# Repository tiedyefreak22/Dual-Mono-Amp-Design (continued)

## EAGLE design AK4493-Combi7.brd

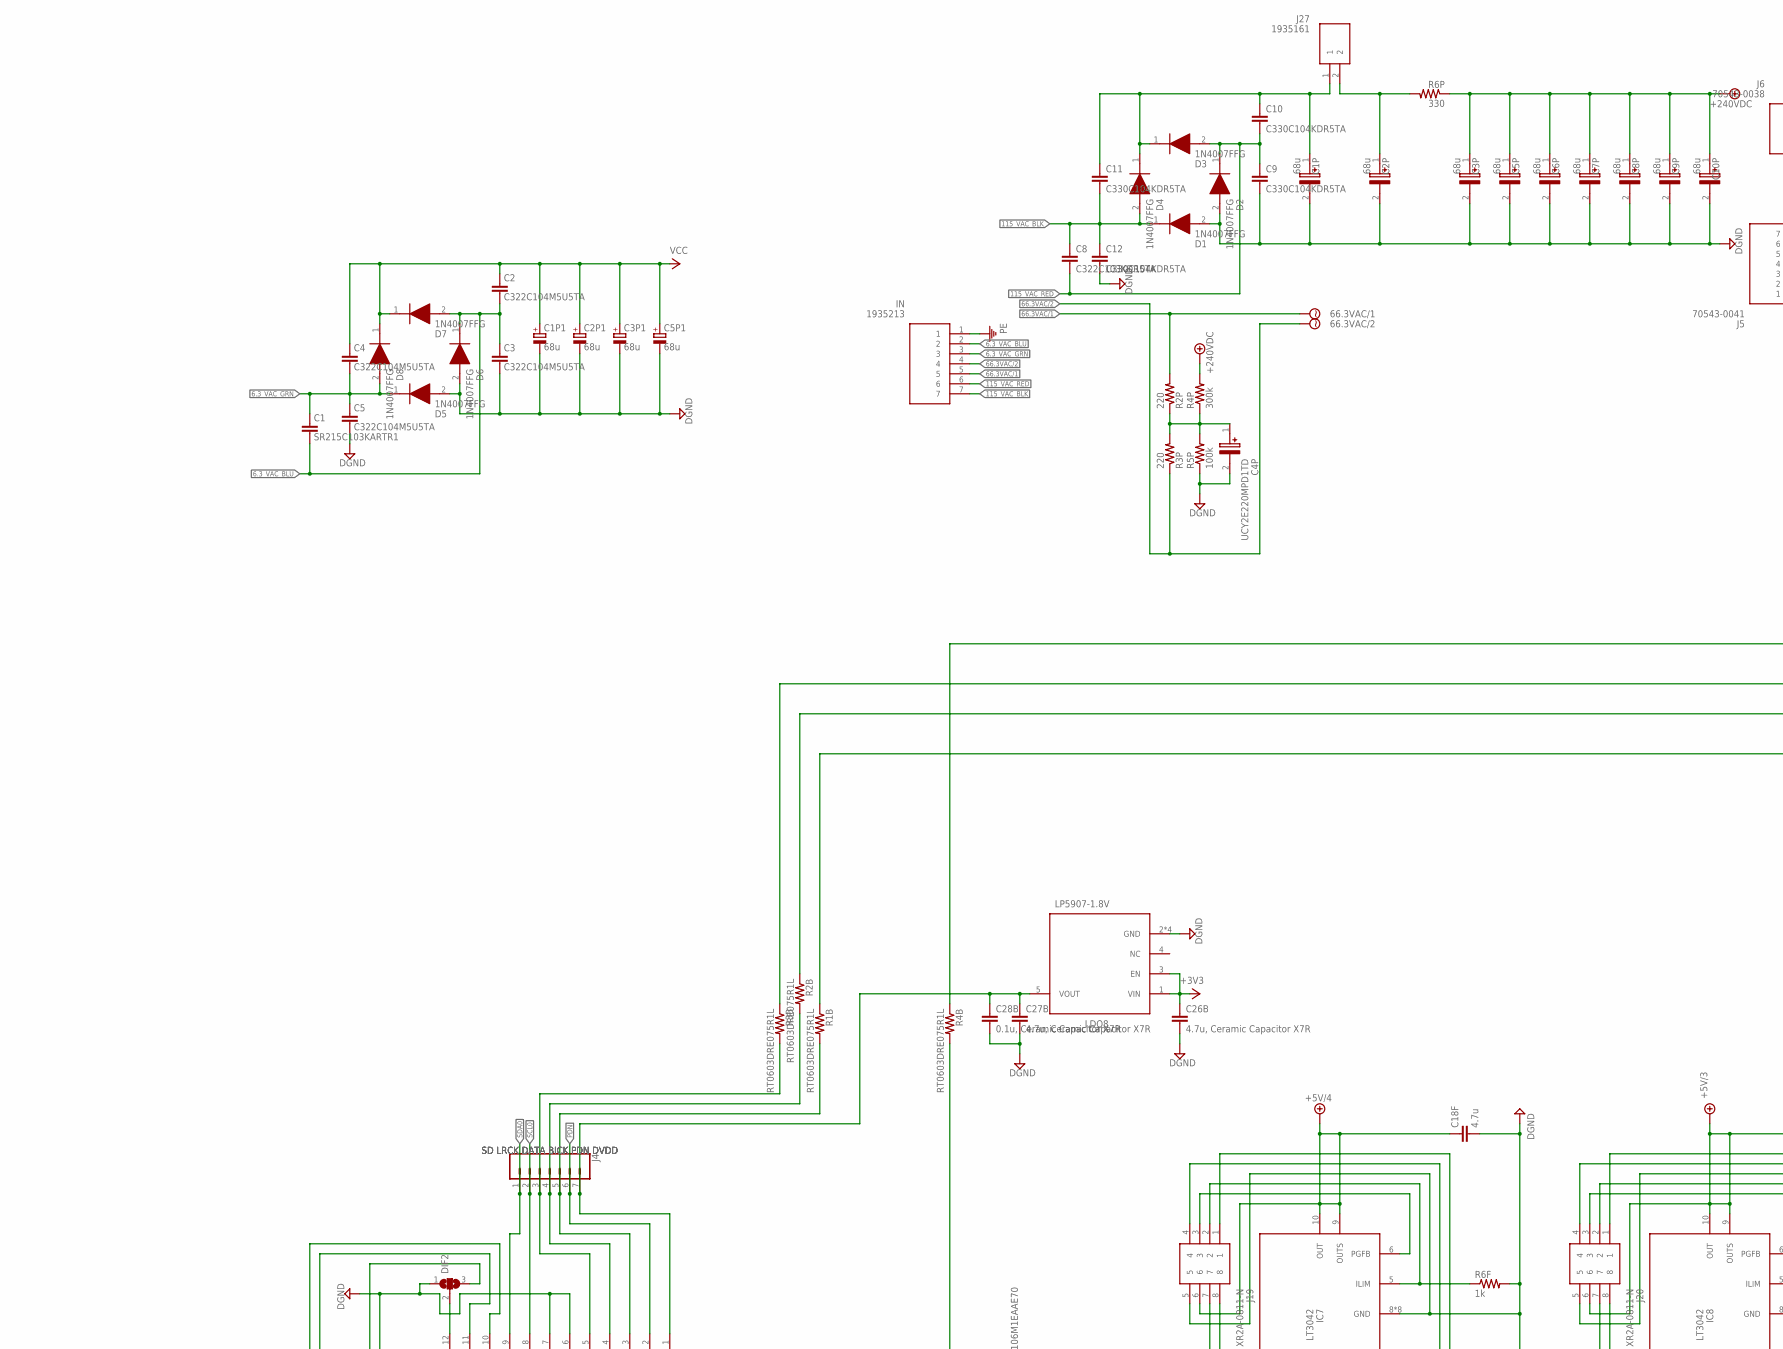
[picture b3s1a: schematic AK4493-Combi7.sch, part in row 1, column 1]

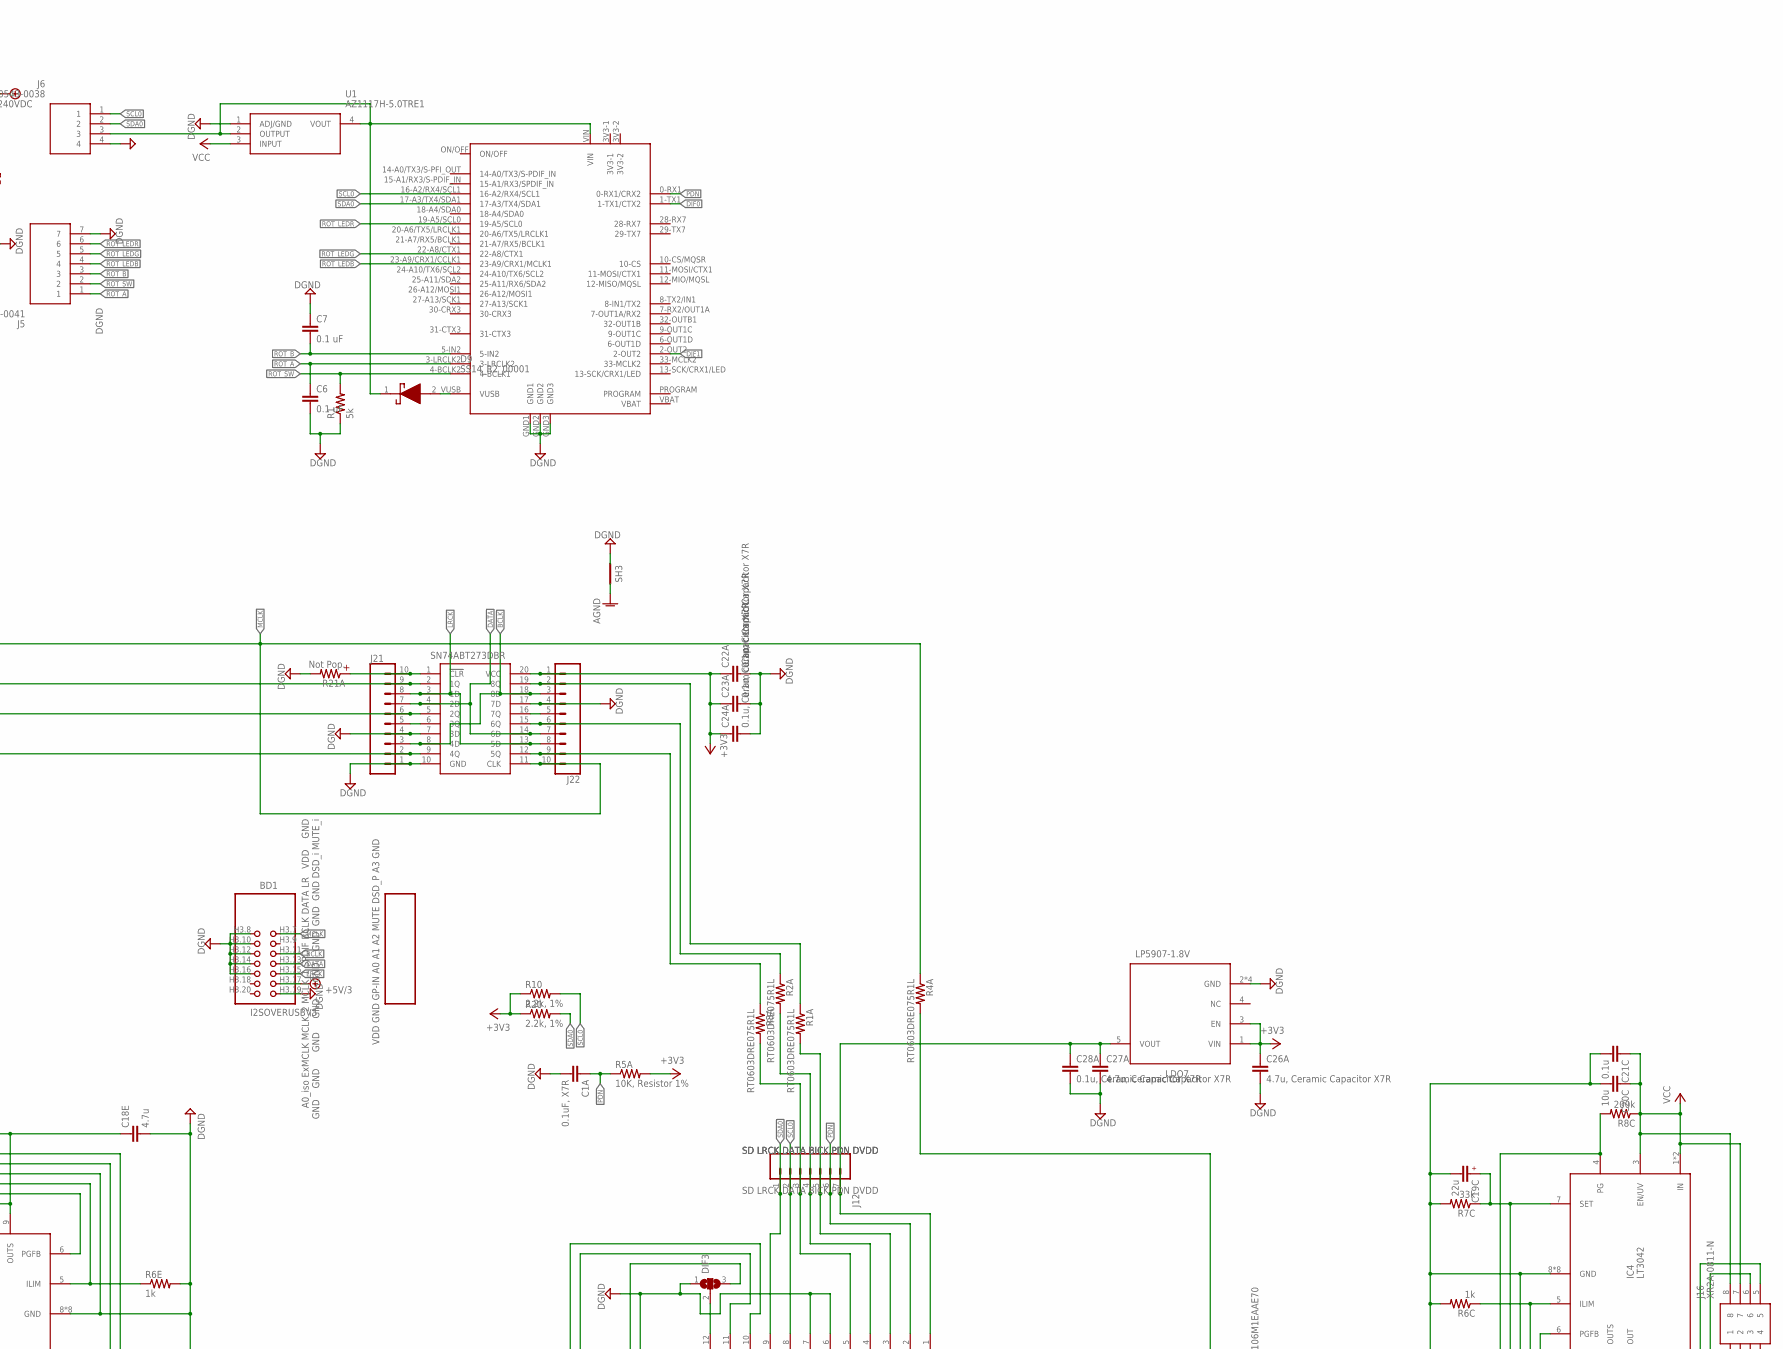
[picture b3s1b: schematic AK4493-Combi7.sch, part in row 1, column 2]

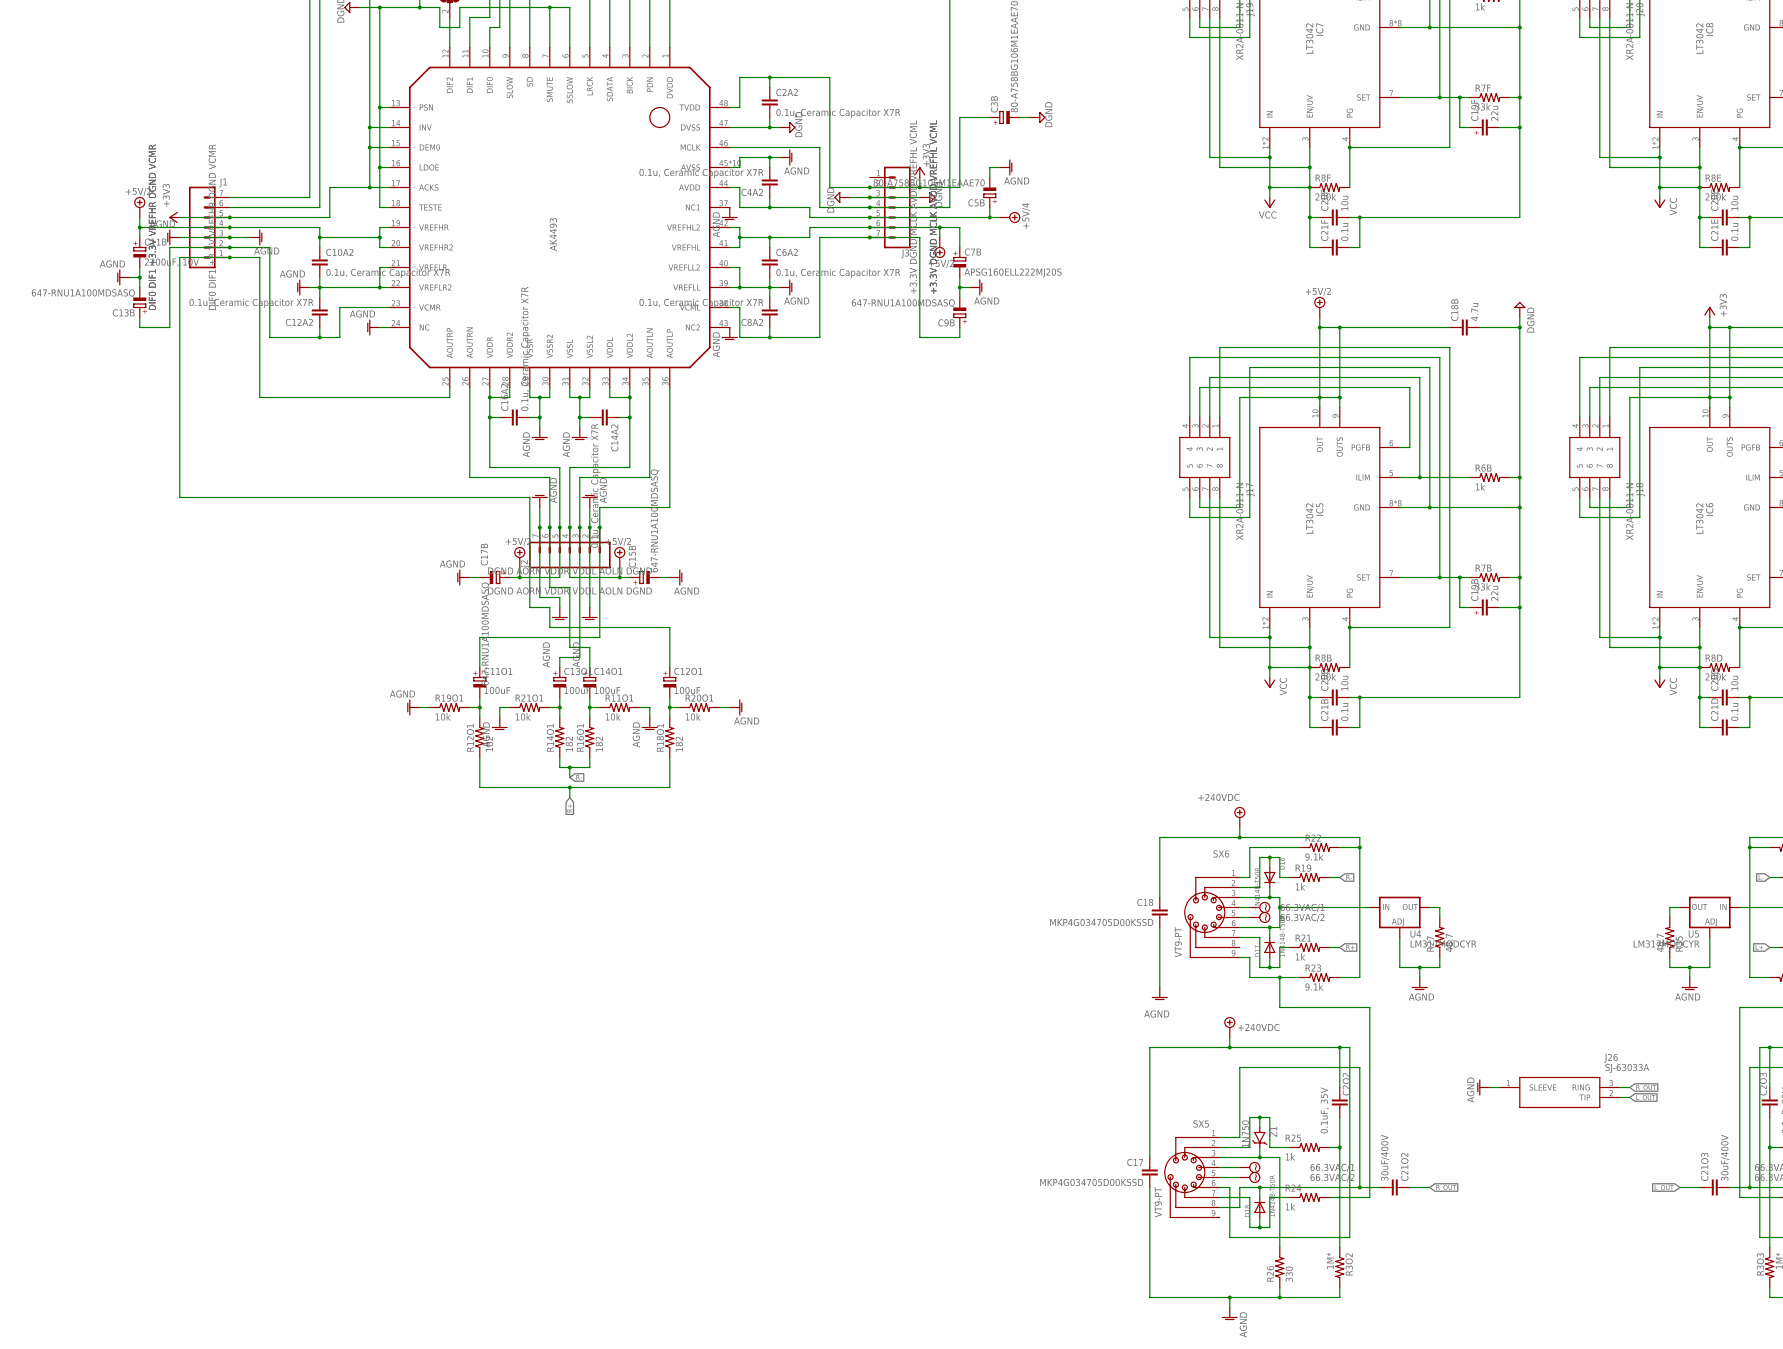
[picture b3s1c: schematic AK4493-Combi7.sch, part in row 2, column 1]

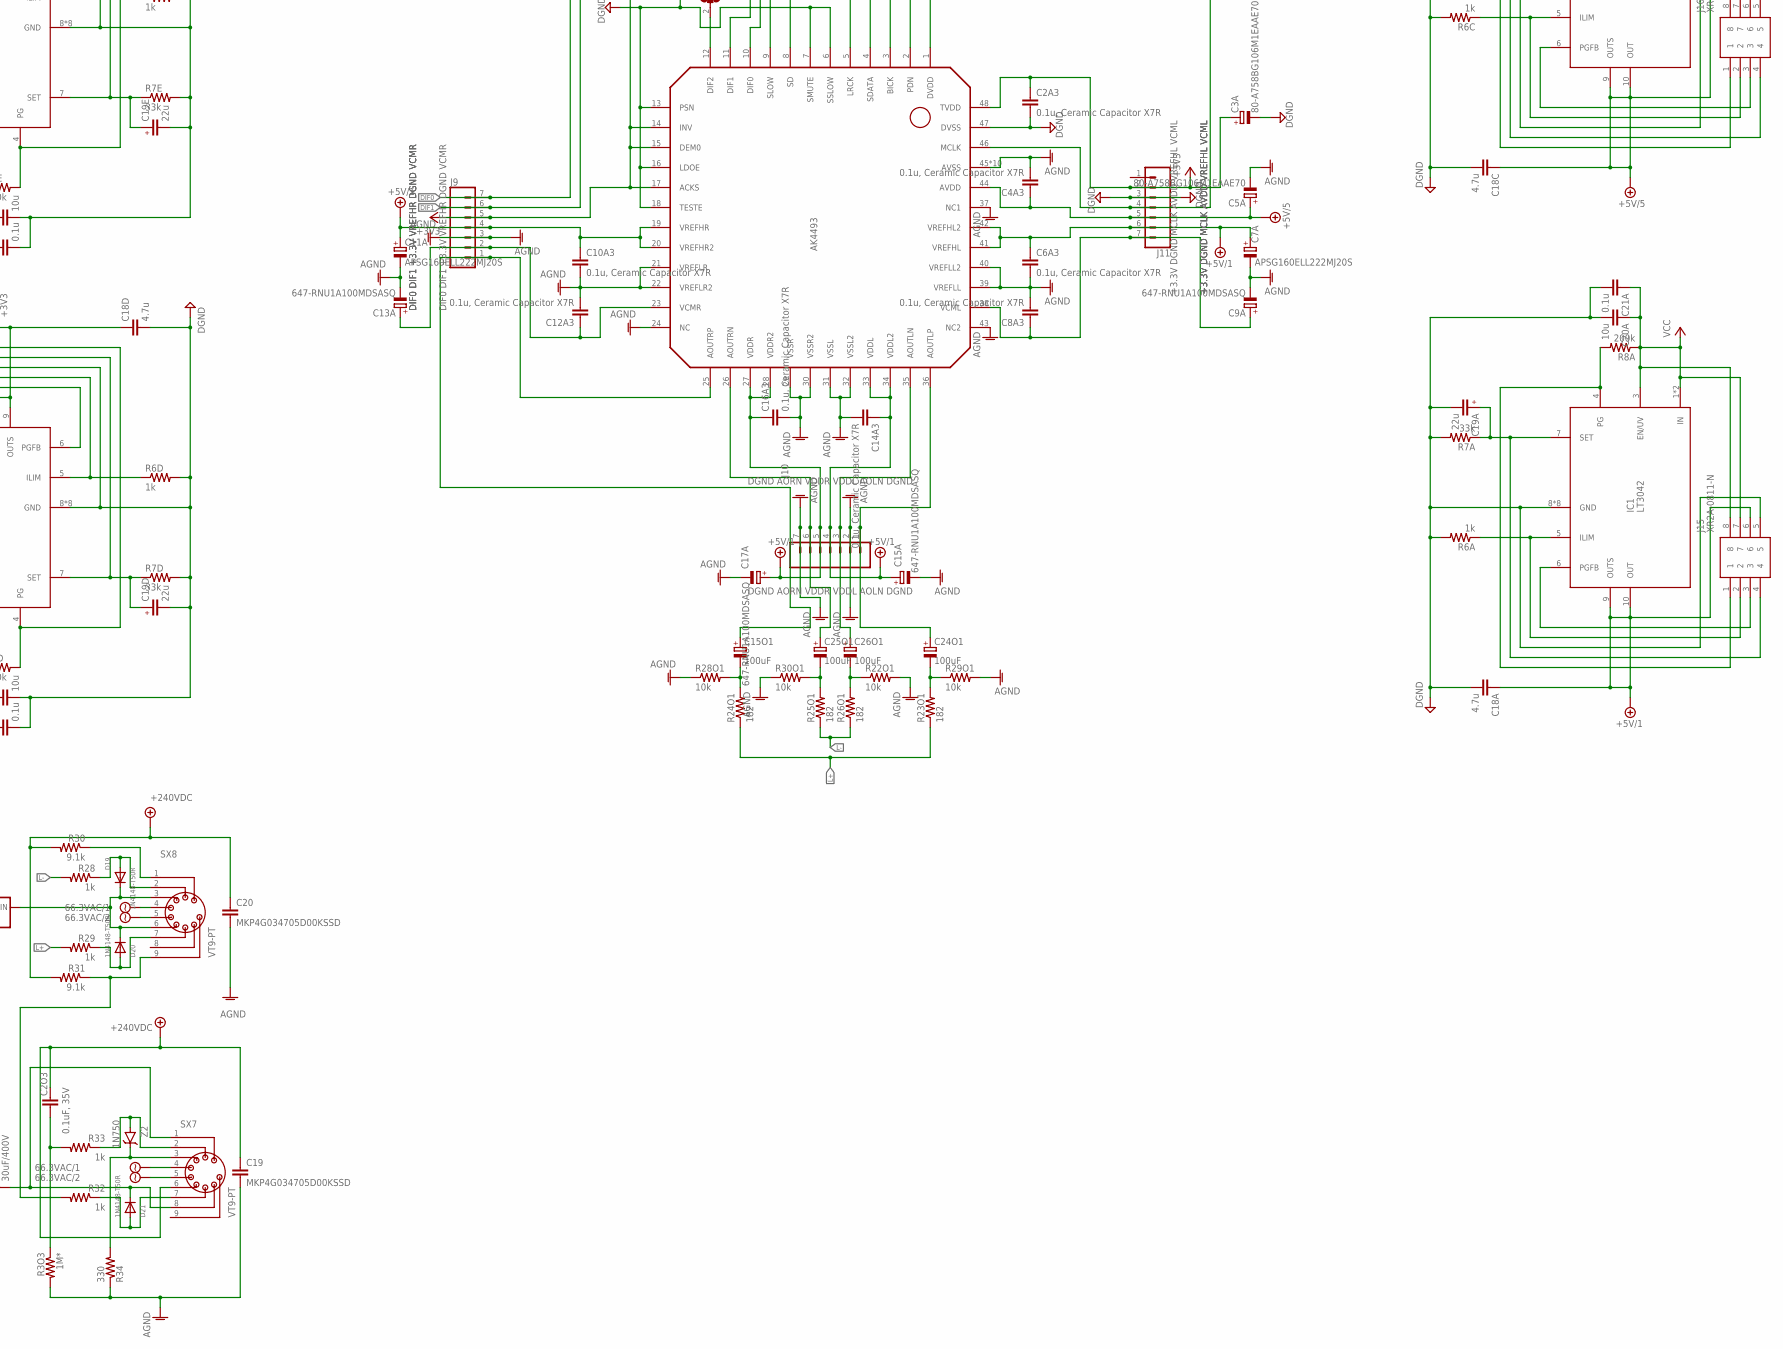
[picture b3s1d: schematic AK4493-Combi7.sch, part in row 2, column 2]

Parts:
BD1: I2SOVERUSBV3
C1: SR215C103KARTR1; SR211C104KARTR1
C1A: 0.1uF, X7R; CAPC2012X135N
C1P, C2P, C3P, C5P, C6P, C7P, C8P, C9P, C10P: 68u; CAPPRD750W80D1475H4700
C1P1, C2P1, C3P1, C5P1: 68u; CAPPRD750W80D1825H3750
C2, C3, C4, C5: C322C104M5U5TA; C322C104K1R5TA
C2A2, C2A3, C4A2, C4A3, C6A2, C6A3, C8A2, C8A3, C10A2, C10A3, C12A2, C12A3, C14A2, C14A3, C16A2, C16A3: 0.1u, Ceramic Capacitor X7R; CAPC1608X95N
C2O2, C2O3: 0.1uF, 35V; MKS4B031002A00JC00
C3A: 80-A758BG106M1EAAE70; CAPPRD150W45D450H600
C3B, C5A, C5B: 80-A758BG106M1EAAE70; CAPPRD200W55D500H800
C4P: UCY2E220MPD1TD; CAPPRD500W60D1025H1750
C6, C7: 0.1 uF; CAPC2012X135N
C7A, C7B, C11A: APSG160ELL222MJ20S; CAPPRD500W60D1025H2150
C8: C322C103KDR5TA; C322C101JCG5TA7301
C9, C10, C11, C12: C330C104KDR5TA
C9A, C9B, C13A, C13B, C15A, C15B, C17A, C17B: 647-RNU1A100MDSASQ; CAPPRD150W45D450H600
C11B: 2200uF, 10V; CAPPRD500W60D1025H2150
C11O1, C12O1, C13O1, C14O1, C15O1, C24O1, C25O1, C26O1: 100uF; CAPPRD350W60D825H1300
C17, C18, C19, C20: MKP4G034705D00KSSD
C18A, C18B, C18C, C18D, C18E, C18F: 4.7u; CAPC2013X140N
C19A, C19B, C19C, C19D, C19E, C19F: 22u; C1206
C20A, C20B, C20C, C20D, C20E, C20F: 10u; CAPC2012X135N
C21A, C21B, C21C, C21D, C21E, C21F: 0.1u; CAPC2012X135N
C21O2, C21O3: 30uF/400V; DCP4G053006ID2KSSD
C22A, C23A, C24A, C28A, C28B: 0.1u, Ceramic Capacitor X7R; CAPC2012X135N
C26A, C26B, C27A, C27B: 4.7u, Ceramic Capacitor X7R; CAPC2013X140N
D1, D2, D3, D4, D5, D6, D7, D8: 1N4007FFG; DIOAD1405W86L465D235
D9: SS14_R2_00001; DIOM5027X244N
D16, D17, D18, D19, D20, D21: 1N4148-T50R; DIOAD1068W53L380D172
DIF2, DIF3: SJ2W; SJ_2
IC1, IC4, IC5, IC6, IC7, IC8: LT3042; SOP50P490X110-11N
IC3, IC9: AK4493; LQFP48_
IC4A: SN74ABT273DBR; SOP65P780X200-20N
IN: 1935213
J1, J2, J3, J4, J9, J10, J11, J12: CONN_07; 1X07
J5: 70543-0041; SHDR7W64P0X254_1X7_2033X508X11
J6: 70543-0038; SHDR4W64P0X254_1X4_1271X660X11
J15, J16, J17, J18, J19, J20: XR2A-0811-N; DIPS762W51P254L1016H390Q8N
J21, J22: CONN_10"; 1X10
J26: SJ-63033A; SJ63033A
J27: 1935161
LDO7, LDO8: LP5907-1.8V; SOT95P280X145-5N
R1: 5k; ERJP06D1000V
R1A, R1B, R2A, R2B, R3A, R3B, R4A, R4B: RT0603DRE075R1L; RESC1608X55N
R2P, R3P: 220; 0411/15
R3O2, R3O3: 1M*; 0207/10
R4P: 300k; 0411/15
R5A: 10K, Resistor 1%; RESC2012X50N
R5P: 100k; 0411/15
R6A, R6B, R6C, R6D, R6E, R6F: 1k; RESC2012X60N
R6P: 330; 0411/15
R7A, R7B, R7C, R7D, R7E, R7F: 33k; R0805
R8A, R8B, R8C, R8D, R8E, R8F: 200k; R0805
R10, R20: 2.2k, 1%; RCS0805_E3
R11O1, R19O1, R20O1, R21O1, R22O1, R28O1, R29O1, R30O1: 10k; 0207/10
R12O1, R14O1, R16O1, R18O1, R23O1, R24O1, R25O1, R26O1: 182; 0207/10
R19, R21, R24, R25, R28, R29, R32, R33: 1k; 0207/10
R21A: Not Pop.; R0805-POL
R22, R23, R30, R31: 9.1k; 0411/15
R26, R34: 330; 0207/10
R27, R35: 48.7; 0207/10
SH3: SHORTA5; SHORT_ALL-50
SX5, SX6, SX7, SX8: VT9-PT
U1: AZ1117H-5.0TRE1; SOT230P700X180-4N@1
U4, U5: LM317MQDCYR; SOT230P700X180-4N
U$1: TEENSY40
Z1, Z2: 1N750; DIOAD1256W56L444D203

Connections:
6.3_VAC_BLU: C1.2, C2.2, C3.1, D6.1 (K), D7.2 (A), IN.2
6.3_VAC_GRN: C1.1, C4.2, C5.1, D5.1 (K), D8.2 (A), IN.3
66.3VAC/1: IN.5, R2P.2, SX5.4, SX6.4, SX7.4, SX8.4
66.3VAC/2: IN.4, R3P.1, SX5.5, SX6.5, SX7.5, SX8.5
115_VAC_BLK: C8.1, C11.2, C12.1, D1.1 (K), D4.2 (A), IN.7
115_VAC_RED: C8.2, C9.1, C10.2, D2.1 (K), D3.2 (A), IN.6
+3V3: C2A2.1, C2A3.1, C3A.1 (+), C3B.1 (+), C18D.1, C22A.1, C23A.1, C24A.1, C26A.1, C26B.1, DIF2.3, DIF3.3, IC3.14 (INV), IC3.15 (DEM0), IC3.17 (ACKS), IC3.48 (TVDD), IC4A.20 (VCC), IC6.9 (OUTS), IC6.10 (OUT), IC9.14 (INV), IC9.15 (DEM0), IC9.17 (ACKS), IC9.48 (TVDD), J1.5, J3.2, J9.5, J11.2, J18.6, J22.1, LDO7.1 (VIN), LDO7.3 (EN), LDO8.1 (VIN), LDO8.3 (EN), R5A.2, R10.1, R20.1
+5V/1: C6A3.1, C7A.1 (+), C10A3.1, C11A.1 (+), C14A3.1, C15A.1 (+), C16A3.1, C17A.1 (+), C18A.1, IC1.9 (OUTS), IC1.10 (OUT), IC9.19 (VREFHR), IC9.20 (VREFHR2), IC9.27 (VDDR), IC9.28 (VDDR2), IC9.33 (VDDL), IC9.34 (VDDL2), IC9.41 (VREFHL), IC9.42 (VREFHL2), J9.4, J10.4, J10.5, J11.6, J15.6
+5V/2: C6A2.1, C7B.1 (+), C10A2.1, C11B.1 (+), C14A2.1, C15B.1 (+), C16A2.1, C17B.1 (+), C18B.1, IC3.19 (VREFHR), IC3.20 (VREFHR2), IC3.27 (VDDR), IC3.28 (VDDR2), IC3.33 (VDDL), IC3.34 (VDDL2), IC3.41 (VREFHL), IC3.42 (VREFHL2), IC5.9 (OUTS), IC5.10 (OUT), J1.4, J2.4, J2.5, J3.6, J17.6
+5V/3: BD1.H3.17, C18E.1, IC8.9 (OUTS), IC8.10 (OUT), J20.6
+5V/4: C4A2.1, C5B.1 (+), C18F.1, IC3.44 (AVDD), IC7.9 (OUTS), IC7.10 (OUT), J3.5, J19.6
+5V/5: C4A3.1, C5A.1 (+), C18C.1, IC4.9 (OUTS), IC4.10 (OUT), IC9.44 (AVDD), J11.5, J16.6
+240VDC: C2O2.1, C2O3.1, C3P.1 (+), C5P.1 (+), C6P.1 (+), C7P.1 (+), C8P.1 (+), C9P.1 (+), C10P.1 (+), C17.1, C18.1, C19.1, C20.1, R4P.2, R6P.1, R22.2, R23.2, R30.2, R31.2, SX5.6, SX7.6
AGND: C4A2.2, C4A3.2, C5A.2 (-), C5B.2 (-), C6A2.2, C6A3.2, C7A.2 (-), C7B.2 (-), C8A2.2, C8A3.2, C9A.2 (-), C9B.2 (-), C10A2.2, C10A3.2, C11A.2 (-), C11B.2 (-), C12A2.2, C12A3.2, C13A.2 (-), C13B.2 (-), C14A2.2, C14A3.2, C15A.2 (-), C15B.2 (-), C16A2.2, C16A3.2, C17.2, C17A.2 (-), C17B.2 (-), C18.2, C19.2, C20.2, IC3.21 (VREFLR), IC3.22 (VREFLR2), IC3.24 (NC), IC3.29 (VSSR), IC3.30 (VSSR2), IC3.31 (VSSL), IC3.32 (VSSL2), IC3.37 (NC1), IC3.39 (VREFLL), IC3.40 (VREFLL2), IC3.43 (NC2), IC3.45 (AVSS), IC3.P$1 (AVSS), IC3.P$2 (AVSS), IC3.P$4 (AVSS), IC3.P$6 (AVSS), IC3.P$8 (AVSS), IC3.P$10 (AVSS), IC3.P$17 (AVSS), IC3.P$18 (AVSS), IC3.P$25 (AVSS), IC9.21 (VREFLR), IC9.22 (VREFLR2), IC9.24 (NC), IC9.29 (VSSR), IC9.30 (VSSR2), IC9.31 (VSSL), IC9.32 (VSSL2), IC9.37 (NC1), IC9.39 (VREFLL), IC9.40 (VREFLL2), IC9.43 (NC2), IC9.45 (AVSS), IC9.P$1 (AVSS), IC9.P$2 (AVSS), IC9.P$4 (AVSS), IC9.P$6 (AVSS), IC9.P$8 (AVSS), IC9.P$10 (AVSS), IC9.P$17 (AVSS), IC9.P$18 (AVSS), IC9.P$25 (AVSS), J1.3, J2.2, J2.7, J9.3, J10.2, J10.7, J26.1 (SLEEVE), R3O2.2, R3O3.2, R11O1.2, R19O1.1, R20O1.2, R21O1.1, R22O1.2, R26.1, R27.1, R28O1.1, R29O1.2, R30O1.1, R34.1, R35.1, SH3.2, U4.1 (ADJ), U5.1 (ADJ)
BCLK: BD1.H3.11, IC4A.8 (4D), IC4A.18 (8D), J21.3, J22.3
DATA: BD1.H3.13, IC4A.4 (2D), IC4A.14 (6D), J21.7, J22.7
DGND: BD1.H3.8, BD1.H3.10, BD1.H3.12, BD1.H3.14, BD1.H3.16, BD1.H3.19, C1A.2, C1P.2 (-), C1P1.2 (-), C2A2.2, C2A3.2, C2P.2 (-), C2P1.2 (-), C3.2, C3A.2 (-), C3B.2 (-), C3P.2 (-), C3P1.2 (-), C4P.2 (-), C5.2, C5P.2 (-), C5P1.2 (-), C6.2, C6P.2 (-), C7.1, C7P.2 (-), C8P.2 (-), C9.2, C9P.2 (-), C10P.2 (-), C12.2, C18A.2, C18B.2, C18C.2, C18D.2, C18E.2, C18F.2, C19A.2, C19A.3 (2), C19B.2, C19B.3 (2), C19C.2, C19C.3 (2), C19D.2, C19D.3 (2), C19E.2, C19E.3 (2), C19F.2, C19F.3 (2), C20A.2, C20B.2, C20C.2, C20D.2, C20E.2, C20F.2, C21A.2, C21B.2, C21C.2, C21D.2, C21E.2, C21F.2, C22A.2, C23A.2, C24A.2, C26A.2, C26B.2, C27A.2, C27B.2, C28A.2, C28B.2, D1.2 (A), D2.2 (A), D5.2 (A), D6.2 (A), DIF2.1, DIF3.1, IC1.8 (GND), IC1.11 (GND), IC1.P$1 (GND), IC1.P$2 (GND), IC1.P$3 (GND), IC1.P$4 (GND), IC1.P$5 (GND), IC1.P$6 (GND), IC3.6 (SSLOW), IC3.7 (SMUTE), IC3.13 (PSN), IC3.16 (LDOE), IC3.18 (TESTE), IC3.47 (DVSS), IC4.8 (GND), IC4.11 (GND), IC4.P$1 (GND), IC4.P$2 (GND), IC4.P$3 (GND), IC4.P$4 (GND), IC4.P$5 (GND), IC4.P$6 (GND), IC4A.7 (3D), IC4A.10 (GND), IC4A.17 (7D), IC5.8 (GND), IC5.11 (GND), IC5.P$1 (GND), IC5.P$2 (GND), IC5.P$3 (GND), IC5.P$4 (GND), IC5.P$5 (GND), IC5.P$6 (GND), IC6.8 (GND), IC6.11 (GND), IC6.P$1 (GND), IC6.P$2 (GND), IC6.P$3 (GND), IC6.P$4 (GND), IC6.P$5 (GND), IC6.P$6 (GND), IC7.8 (GND), IC7.11 (GND), IC7.P$1 (GND), IC7.P$2 (GND), IC7.P$3 (GND), IC7.P$4 (GND), IC7.P$5 (GND), IC7.P$6 (GND), IC8.8 (GND), IC8.11 (GND), IC8.P$1 (GND), IC8.P$2 (GND), IC8.P$3 (GND), IC8.P$4 (GND), IC8.P$5 (GND), IC8.P$6 (GND), IC9.6 (SSLOW), IC9.7 (SMUTE), IC9.13 (PSN), IC9.16 (LDOE), IC9.18 (TESTE), IC9.47 (DVSS), J3.3, J5.7, J6.4, J11.3, J15.5, J16.5, J17.5, J18.5, J19.5, J20.5, J21.1, J21.4, J22.4, LDO7.2 (GND), LDO7.6 (GND), LDO7.7 (GND), LDO7.8 (GND), LDO8.2 (GND), LDO8.6 (GND), LDO8.7 (GND), LDO8.8 (GND), R1.1, R5P.1, R6A.2, R6B.2, R6C.2, R6D.2, R6E.2, R6F.2, R7A.2, R7B.2, R7C.2, R7D.2, R7E.2, R7F.2, R21A.2, R21A.3 (2), SH3.1, U1.1 (ADJ/GND), U$1.GND1, U$1.GND2, U$1.GND3
DIF0: IC9.10 (DIF0), J9.7, U$1.1-TX1 (1-TX1/CTX2)
DIF1: IC9.11 (DIF1), J9.6, U$1.2-OUT2
L+: R23O1.1, R24O1.1, R29.2
L-: R25O1.1, R26O1.1, R28.2
LRCK: BD1.H3.15, IC4A.3 (1D), IC4A.13 (5D), J21.8, J22.8
L_OUT: C21O3.1, J26.2 (TIP)
MCLK: BD1.H3.7, IC4A.11 (CLK), J22.10, R4A.1, R4B.1
unnamed: IC4A.1 (!CLR), J21.10, R21A.1
unnamed: C8A2.1, C9B.1 (+), IC3.38 (VCML), J3.7
unnamed: IC4A.6 (3Q), J21.5
unnamed: IC4A.16 (7Q), J22.5
unnamed: C19A.1, IC1.7 (SET), J15.4, R7A.1
unnamed: D9.2 (A), U$1.VUSB
unnamed: IC5.4 (PG), J17.1, R8B.2
unnamed: IC5.6 (PGFB), J17.3
unnamed: C12A3.1, C13A.1 (+), IC9.23 (VCMR), J9.2
unnamed: IC3.5 (LRCK), J4.3, R3B.2
unnamed: IC9.46 (MCLK), J11.4, R4A.2
unnamed: IC5.5 (ILIM), J17.2, R6B.1
unnamed: IC4A.19 (8Q), J22.2, R1A.1
unnamed: IC4A.15 (6Q), J22.6, R2A.1
unnamed: IC4A.12 (5Q), J22.9, R3A.1
unnamed: IC3.4 (SDATA), J4.4, R2B.2
unnamed: C27A.1, C28A.1, IC9.1 (DVDD), J12.7, LDO7.5 (VOUT)
unnamed: IC3.3 (BICK), J4.5, R1B.2
unnamed: C27B.1, C28B.1, IC3.1 (DVDD), J4.7, LDO8.5 (VOUT)
unnamed: IC4A.9 (4Q), J21.2, R1B.1
unnamed: IC4A.5 (2Q), J21.6, R2B.1
unnamed: IC4A.2 (1Q), J21.9, R3B.1
unnamed: IC6.4 (PG), J18.1, R8D.2
unnamed: IC7.5 (ILIM), J19.2, R6F.1
unnamed: C14O1.1 (+), IC3.26 (AOUTRN), J2.6
unnamed: IC6.6 (PGFB), J18.3
unnamed: D9.1 (K), J6.3, U1.2 (OUTPUT), U1.4 (VOUT), U$1.VIN
unnamed: IC6.5 (ILIM), J18.2, R6D.1
unnamed: IC1.6 (PGFB), J15.3
unnamed: C19D.1, IC6.7 (SET), J18.4, R7D.1
unnamed: IC7.4 (PG), J19.1, R8F.2
unnamed: C13O1.1 (+), IC3.35 (AOUTLN), J2.3
unnamed: C19F.1, IC7.7 (SET), J19.4, R7F.1
unnamed: IC8.4 (PG), J20.1, R8E.2
unnamed: IC8.6 (PGFB), J20.3
unnamed: IC8.5 (ILIM), J20.2, R6E.1
unnamed: C19E.1, IC8.7 (SET), J20.4, R7E.1
unnamed: IC3.46 (MCLK), J3.4, R4B.2
unnamed: IC3.11 (DIF1), J1.6
unnamed: IC3.10 (DIF0), J1.7
unnamed: C1P.1 (+), C10.1, C11.1, D3.1 (K), D4.1 (K), J27.1
unnamed: C2P.1 (+), J27.2, R6P.2
unnamed: C4P.1 (+), R2P.1, R3P.2, R4P.1, R5P.2
unnamed: C21O2.2, D18.1 (C), SX5.1, SX5.8
unnamed: C11O1.2 (-), R12O1.2, R19O1.2
unnamed: C12O1.2 (-), R18O1.2, R20O1.1
unnamed: C14O1.2 (-), R11O1.1, R16O1.2
unnamed: C13O1.2 (-), R14O1.2, R21O1.2
unnamed: C24O1.1 (+), IC9.36 (AOUTLP), J10.1
unnamed: C26O1.1 (+), IC9.35 (AOUTLN), J10.3
unnamed: C15O1.1 (+), IC9.25 (AOUTRP), J9.1
unnamed: C25O1.1 (+), IC9.26 (AOUTRN), J10.6
unnamed: C15O1.2 (-), R24O1.2, R28O1.2
unnamed: IC9.5 (LRCK), J12.3, R3A.2
unnamed: IC9.4 (SDATA), J12.4, R2A.2
unnamed: IC9.3 (BICK), J12.5, R1A.2
unnamed: C24O1.2 (-), R23O1.2, R29O1.1
unnamed: C8A3.1, C9A.1 (+), IC9.38 (VCML), J11.7
unnamed: C19B.1, IC5.7 (SET), J17.4, R7B.1
unnamed: IC1.4 (PG), J15.1, R8A.2
unnamed: C26O1.2 (-), R22O1.1, R26O1.2
unnamed: C19C.1, IC4.7 (SET), J16.4, R7C.1
unnamed: IC4.6 (PGFB), J16.3
unnamed: IC4.5 (ILIM), J16.2, R6C.1
unnamed: IC1.5 (ILIM), J15.2, R6A.1
unnamed: IC7.6 (PGFB), J19.3
unnamed: IC4.4 (PG), J16.1, R8C.2
unnamed: C11O1.1 (+), IC3.36 (AOUTLP), J2.1
unnamed: C25O1.2 (-), R25O1.2, R30O1.2
unnamed: C12O1.1 (+), IC3.25 (AOUTRP), J1.1
unnamed: D16.2 (A), R19.1, SX6.2
unnamed: D17.2 (A), R21.1, SX6.7
unnamed: D16.1 (C), D17.1 (C), SX6.3, SX6.6, U4.3 (IN)
unnamed: R22.1, SX6.1
unnamed: R23.1, R24.2, SX6.9
unnamed: R25.1, SX5.2, Z1.2 (A)
unnamed: C2O2.2, R3O2.1, R25.2
unnamed: R26.2, SX5.3, Z1.1 (C)
unnamed: D18.2 (A), R24.1, SX5.7
unnamed: R27.2, U4.2 (OUT), U4.4 (OUT)
unnamed: C21O3.2, D21.1 (C), SX7.1, SX7.8
unnamed: C12A2.1, C13B.1 (+), IC3.23 (VCMR), J1.2
unnamed: D19.2 (A), R28.1, SX8.2
unnamed: DIF2.2, IC3.12 (DIF2)
unnamed: D20.2 (A), R29.1, SX8.7
unnamed: D19.1 (C), D20.1 (C), SX8.3, SX8.6, U5.3 (IN)
unnamed: R30.1, SX8.1
unnamed: R31.1, R32.2, SX8.9
unnamed: R33.1, SX7.2, Z2.2 (A)
unnamed: C2O3.2, R3O3.1, R33.2
unnamed: R34.2, SX7.3, Z2.1 (C)
unnamed: D21.2 (A), R32.1, SX7.7
unnamed: R35.2, U5.2 (OUT), U5.4 (OUT)
unnamed: DIF3.2, IC9.12 (DIF2)
PDN: C1A.1, IC3.2 (PDN), IC9.2 (PDN), J4.6, J12.6, R5A.1, U$1.0-RX1 (0-RX1/CRX2)
PE: IN.1
R+: R12O1.1, R18O1.1, R21.2
R-: R14O1.1, R16O1.1, R19.2
ROT_A: C6.1, J5.1, U$1.3-LRCLK2
ROT_B: C7.2, J5.3, U$1.5-IN2
ROT_LEDB: J5.4, U$1.23-A9/CRX1/CCLK1 (23-A9/CRX1/MCLK1)
ROT_LEDG: J5.5, U$1.22-A8/CTX1
ROT_LEDR: J5.6, U$1.19-A5/SCL0
ROT_SW: J5.2, R1.2, U$1.4-BCLK2 (4-BCLK1)
R_OUT: C21O2.1, J26.3 (RING)
SCL0: IC3.8 (SD), IC9.8 (SD), J4.2, J6.1, J12.2, R10.2, U$1.16-A2/RX4/SCL1
SDA0: IC3.9 (SLOW), IC9.9 (SLOW), J4.1, J6.2, J12.1, R20.2, U$1.17-A3/TX4/SDA1
VCC: C1P1.1 (+), C2.1, C2P1.1 (+), C3P1.1 (+), C4.1, C5P1.1 (+), C20A.1, C20B.1, C20C.1, C20D.1, C20E.1, C20F.1, C21A.1, C21B.1, C21C.1, C21D.1, C21E.1, C21F.1, D7.1 (K), D8.1 (K), IC1.1 (IN), IC1.2 (IN), IC1.3 (EN/UV), IC4.1 (IN), IC4.2 (IN), IC4.3 (EN/UV), IC5.1 (IN), IC5.2 (IN), IC5.3 (EN/UV), IC6.1 (IN), IC6.2 (IN), IC6.3 (EN/UV), IC7.1 (IN), IC7.2 (IN), IC7.3 (EN/UV), IC8.1 (IN), IC8.2 (IN), IC8.3 (EN/UV), J15.7, J15.8, J16.7, J16.8, J17.7, J17.8, J18.7, J18.8, J19.7, J19.8, J20.7, J20.8, R8A.1, R8B.1, R8C.1, R8D.1, R8E.1, R8F.1, U1.3 (INPUT)

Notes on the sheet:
+3.3V DGND MCLK AVDD VREFHL VCML
DIF0 DIF1 +3.3V VREFHR DGND VCMR
SD LRCK DATA BICK PDN DVDD
DGND AORN VDDR VDDL AOLN DGND

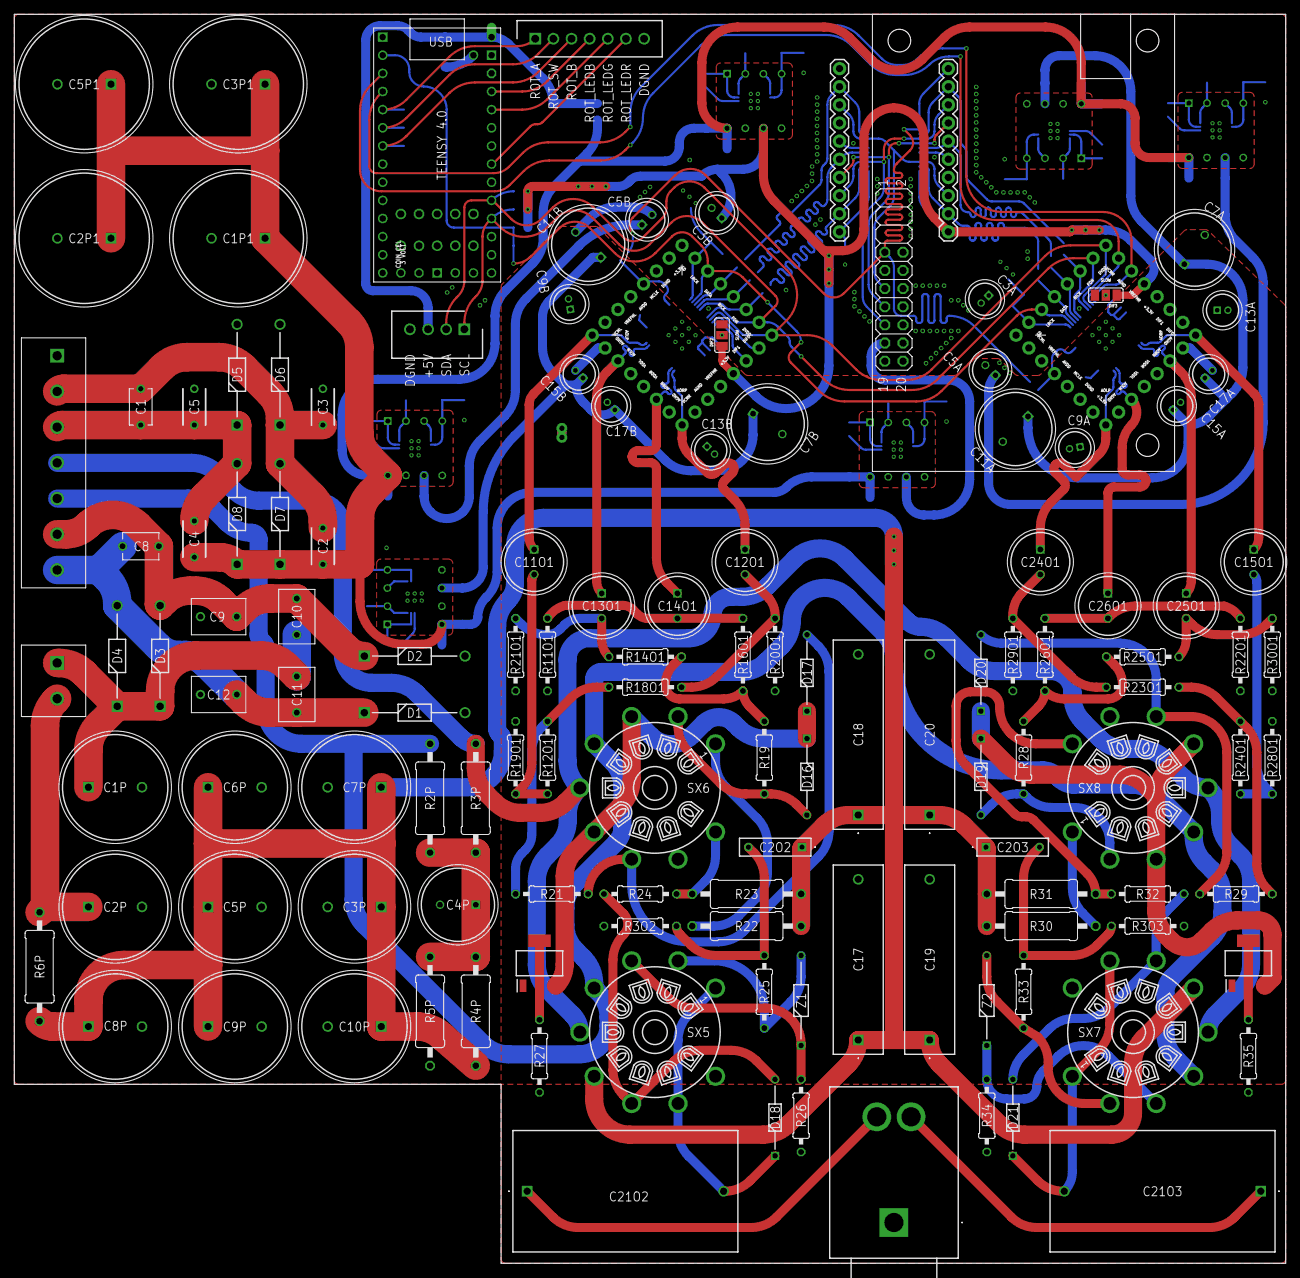
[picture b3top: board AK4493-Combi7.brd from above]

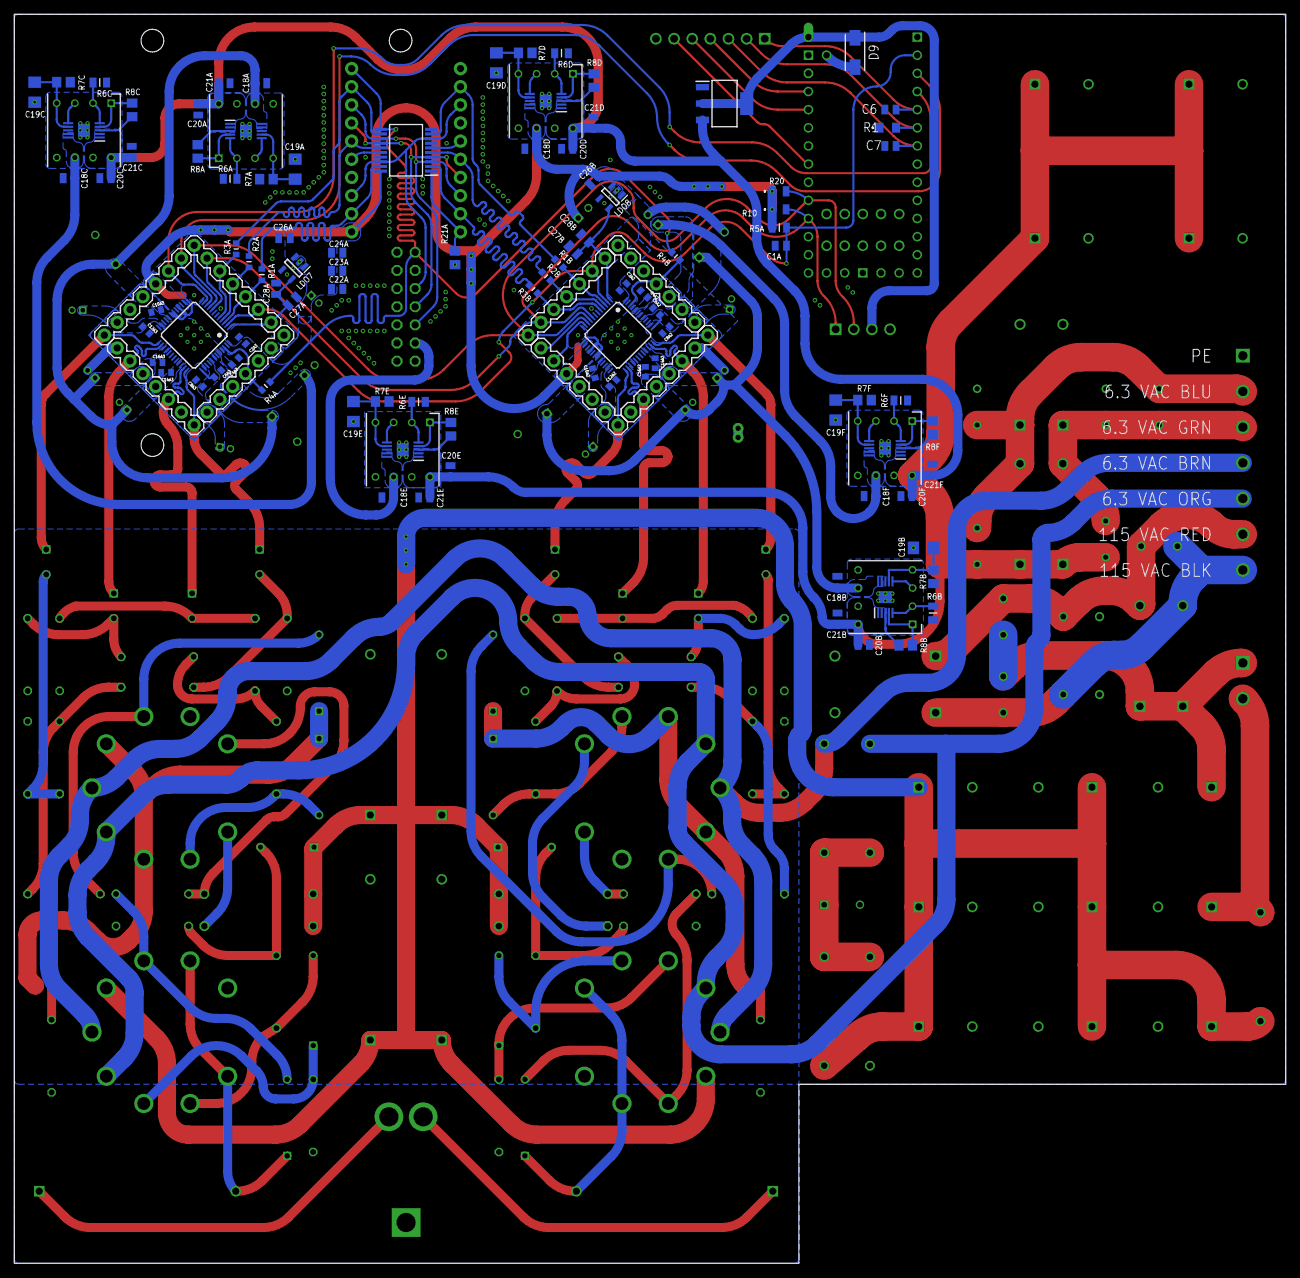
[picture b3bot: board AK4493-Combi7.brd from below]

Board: 2 copper layers, 178.0 x 174.9 mm, 239 parts (110 on the bottom side), 131 nets.

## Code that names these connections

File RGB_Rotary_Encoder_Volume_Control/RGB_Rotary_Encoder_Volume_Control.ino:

// "RGB_Rotary_Encoder"

// HARDWARE CONNECTIONS

// Rotary encoder pin A to digital pin 3*
// Rotary encoder pin B to analog pin 3
// Rotary encoder pin C to ground

// This sketch implements software debounce, but you can further
// improve performance by placing 0.1uF capacitors between
// A and ground, and B and ground.

// Rotary encoder pin 1 (red cathode) to digital pin 10
// Rotary encoder pin 2 (green cathode) to analog pin 1
// Rotary encoder pin 3 (button) to digital pin 4
// Rotary encoder pin 4 (blue cathode) to digital pin 5
// Rotary encoder pin 5 (common anode) to VCC (3.3V or 5V)

// Note that because this is a common anode device,
// the pushbutton requires an external 1K-10K pullDOWN resistor
// to operate.

// * Pins marked with an asterisk should not change because
// they use interrupts on that pin. All other pins can change,
// see the constants below.

// SERIAL MONITOR

// Run this sketch with the serial monitor window set to 9600 baud.

// HOW IT WORKS

// The I/O pins used by the rotary encoder hardware are set up to
// automatically call interrupt functions (rotaryIRQ and buttonIRQ)
// each time the rotary encoder changes states.

// The rotaryIRQ function transparently maintains a counter that
// increments or decrements by one for each detent ("click") of
// the rotary encoder knob. This function also sets a flag
// (rotary_change) to true whenever the counter changes. You can
// check this flag in your main loop() code and perform an action
// when the knob is turned.

// The buttonIRQ function does the same thing for the pushbutton
// built into the rotary encoder knob. It will set flags for
// button_pressed and button_released that you can monitor in your
// main loop() code. There is also a variable for button_downtime
// which records how long the button was held down.

// There is also code in the main loop() that keeps track
// of whether the button is currently being held down and for
// how long. This is useful for "hold button down for five seconds
// to power off"-type situations, which cannot be handled by
// interrupts alone because no interrupts will be called until
// the button is actually released.

#include <Bounce.h>
#include <Encoder.h>

#define ROT_LEDG A8  // green LED
#define ROT_B 5      // rotary A
#define ROT_A 3      // rotary B
#define ROT_SW 4     // rotary puhbutton
#define ROT_LEDB A9  // blue LED
#define ROT_LEDR A5  // red LED
#define TEENSY_LED 13

volatile int rotary_counter = 0;  // current "position" of rotary encoder (increments CW)
volatile int volume = 0;

// // Change these two numbers to the pins connected to your encoder.
// //   Best Performance: both pins have interrupt capability
// //   Good Performance: only the first pin has interrupt capability
// //   Low Performance:  neither pin has interrupt capability
Encoder myEnc(ROT_B, ROT_A);

// Instantiate a Bounce object with a 5 millisecond debounce time
Bounce bouncer = Bounce(ROT_SW, 5);

void setup() {
  pinMode(TEENSY_LED, OUTPUT);
  digitalWrite(TEENSY_LED, 1);
  pinMode(ROT_SW, INPUT);
  // The rotary switch is common anode with external pulldown, do not turn on pullup
  pinMode(ROT_LEDB, OUTPUT);
  pinMode(ROT_LEDG, OUTPUT);
  pinMode(ROT_LEDR, OUTPUT);

  volumeLED(volume);

  Serial.begin(115200);  // Use serial for debugging
  Serial.println("Begin RGB Rotary Encoder Testing");
}

long lastPosition = 0;
const int stepsPerDetent = 2;  // Adjust based on your encoder (common values: 2 or 4)
int messageCounter = 0;        // Tracks how many messages have been processed
bool mute = false;

void loop() {
  // Update the debouncer
  bouncer.update();

  // Get the update value
  int value = bouncer.read();

  // Turn on or off the LED
  if ((value == HIGH) & (mute == false)) {
    Serial.println("Muted");
    setMUTE();
    mute = true;
    delay(1000);  // Small delay for stability
  } else if ((value == HIGH) & (mute == true)) {
    Serial.println("Unmuted");
    volumeLED(volume);
    mute = false;
    delay(1000);  // Small delay for stability
  } else if (volume == 0) {
    setMUTE();
  }

  if (mute == false) {
    long newPosition = myEnc.read();
    int movement = newPosition - lastPosition;

    if (abs(movement) >= stepsPerDetent) {
      messageCounter++;  // Increment the counter

      if (messageCounter % 2 == 1) {  // Only print every second message
        if (newPosition > lastPosition) {
          Serial.println("Rotating Counterclockwise ←");
          if (volume - 1 <= 0) {
            volume = 0;
          } else {
            volume = volume - 1;
          }
          Serial.println(volume);
          volumeLED(volume);
        } else {
          Serial.println("Rotating Clockwise →");
          if (volume + 1 > 50) {
            volume = 50;
          } else {
            volume = volume + 1;
          }
          Serial.println(volume);
          volumeLED(volume);
        }
      }

      lastPosition = newPosition;  // Update position
    }
  }
  delay(5);  // Small delay for stability
}

void setMUTE()
{
  analogWrite(ROT_LEDR, 0);
  analogWrite(ROT_LEDG, 255);
  analogWrite(ROT_LEDB, 255);
}

void volumeLED(int volume)  // Volume from 1 - 50
{
  analogWrite(ROT_LEDR, 0);
  //analogWrite(ROT_LEDG, 255 - round((97 / 50) * volume));
  analogWrite(ROT_LEDG, round(194 / (1 + exp(0.17 * volume)) + 158));
  //analogWrite(ROT_LEDB, round((255 / 50) * volume));
  analogWrite(ROT_LEDB, round(529.031 / (1 + exp(-0.08 * volume)) - 264.516));
}
